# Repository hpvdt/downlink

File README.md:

# downlink
General data downlink system for our vehicles

## Known USB Issue

The STM32F103 series of microcontrollers needs an external 1.5&nbsp;kOhm pullup resistor to the 3.3&nbsp;V supply rail on the D+ line for proper used, as per table 3 in section 2.1 of [AN4879](https://www.st.com/resource/en/application_note/an4879-introduction-to-usb-hardware-and-pcb-guidelines-using-stm32-mcus-stmicroelectronics.pdf). 

This explains why previous boards failed to work with USB communications. The TITAN 2022 board managed to work because there was a 10&nbsp;kOhm resistor for this pullup, likely the minimum needed for this.

There is also no need for the 22&nbsp;Ohm resistors on the USB data lines.

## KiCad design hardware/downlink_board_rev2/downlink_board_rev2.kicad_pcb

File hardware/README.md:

# Hardware

These are the designs for the downlink board.

## USB Issues

After assembling V1.2 of the board, it was found trhat the USB functionality of the chip doesn't work. This issue seems to come from having the chip on the board, as flashing the code on STM32's on dev boards worked as intended. 

Further tests to try and isolate the root cause were inconclusive, installing a new chip didn't help; transplating a working chip from a dev board to this board failed, but worked when returned to its original dev board; running wires from a dev board to the 22 ohm resistors worked. So it seems to just affect chips that are mounted directly on the board.

So there is no known root cause, at least these boards can be used as RPi HATs until revised.

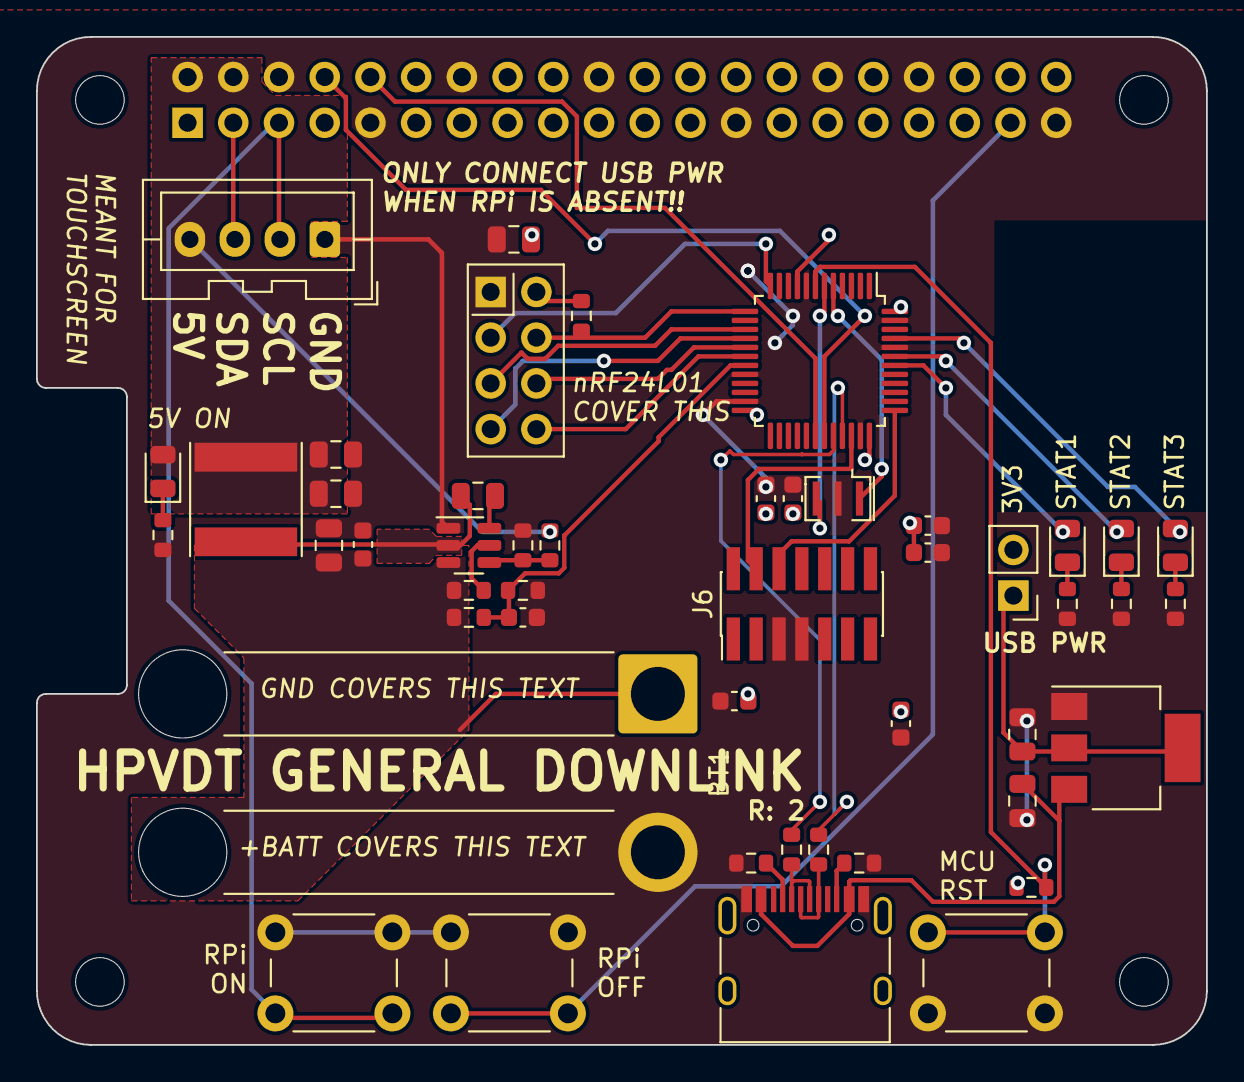
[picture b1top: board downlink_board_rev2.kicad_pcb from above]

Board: 2 copper layers, 65.0 x 56.0 mm, 53 parts (1 on the bottom side), 40 nets.

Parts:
BT1: Battery; SolderWire-2.5sqmm_1x02_P8.8mm_D2.4mm_OD4.4mm_Relief
C1, C2, C14: 10u; C_0805_2012Metric
C3, C8, C9, C10, C11, C13: 100n; C_0603_1608Metric
C4, C6, C7: 22u; C_0805_2012Metric
C5: 100n; C_0805_2012Metric
C12: 10n; C_0603_1608Metric
C15: 1u; C_0603_1608Metric
D1, D2, D3, D4: LED; LED_0805_2012Metric
J1: USB_C_Receptacle_USB2.0; USB_C_Receptacle_HRO_TYPE-C-31-M-12
J2: SCREEN; JST_XA_B04B-XASK-1_1x04_P2.50mm_Vertical
J3: GPIO; PinSocket_2x20_P2.54mm_Vertical
J6: Conn_ST_STDC14; PinHeader_2x07_P1.27mm_Vertical_SMD
JP1: USB_PWR; PinHeader_1x02_P2.54mm_Vertical
L1: 3u3; L_Taiyo-Yuden_NR-60xx
MH1, MH2, MH3, MH4: MountingHole_2.7mm_M2.5
R1, R2: 5.1k; R_0603_1608Metric
R3, R4: 22; R_0603_1608Metric
R5, R7, R13, R14, R16: 10k; R_0603_1608Metric
R6, R15: 54k9; R_0603_1608Metric
R8, R10, R11, R12: 330; R_0603_1608Metric
SW1: RPi_{ON}; SW_PUSH_6mm_H4.3mm
SW2: RPi_{OFF}; SW_PUSH_6mm_H4.3mm
SW3: MCU_{RST}; SW_PUSH_6mm_H4.3mm
U1: AZ1117-3.3; SOT-223-3_TabPin2
U2: TPS563208DDCR; TSOT-23-6
U3: STM32F103C8Tx; LQFP-48_7x7mm_P0.5mm
U4: nRF24L01; nRF24L01_Breakout
Y1: 8M; Resonator_SMD_Murata_CSTxExxV-3Pin_3.0x1.1mm

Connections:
+3.3V: C8.2, C9.2, C10.2, C11.2, C12.2, C14.2, C15.2, J3.1, J3.17, JP1.2 (B), R13.2, R14.2, U3.9 (VDDA), U3.24 (VDD), U3.36 (VDD), U3.48 (VDD), U4.2 (VCC)
+5V: C6.2, C7.2, D2.2 (A), J2.4, J3.2, J3.4, L1.2, R6.1
+BATT: BT1.1 (+), C1.2, C3.2, R5.1, R15.2, U2.3 (VIN)
/BATT_{DIV}: C13.2, R15.1, R16.2, U3.19 (PB1)
/D+: J1.A6 (D+), J1.B6 (D+), R4.1
/D-: J1.A7 (D-), J1.B7 (D-), R3.1
/FB: R6.2, R7.2, U2.4 (VFB)
/GPIO26: J3.37, SW2.2
/MISO: U3.16 (PA6), U4.7 (MISO)
/MOSI: U3.17 (PA7), U4.6 (MOSI)
/RF_{EN}: U3.12 (PA2), U4.3 (CE)
/RF_{INT}: U3.18 (PB0), U4.8 (IRQ)
/RF_{SEL}: R14.1, U3.13 (PA3), U4.4 (~CSN)
/RPi_{RX}: J3.10, U3.30 (PA9)
/RPi_{TX}: J3.8, U3.31 (PA10)
/RST_{MCU}: R13.1, SW3.2, U3.7 (NRST)
/SCK: U3.15 (PA5), U4.5 (SCK)
/SCL: J2.2, J3.5, SW1.2
/SDA: J2.3, J3.3
/SDWIO: J6.4 (JTMS/SWDIO), U3.34 (PA13)
/STATUS_{1}: D1.2 (A), U3.42 (PB6)
/STATUS_{2}: D3.2 (A), U3.43 (PB7)
/STATUS_{3}: D4.2 (A), U3.45 (PB8)
/SWCLK: J6.6 (JCLK/SWCLK), U3.37 (PA14)
/USB_D+: R4.2, U3.33 (PA12)
/USB_D-: R3.2, U3.32 (PA11)
GND: BT1.2 (-), C1.1, C2.1, C3.1, C4.1, C6.1, C7.1, C8.1, C9.1, C10.1, C11.1, C12.1, C13.1, C14.1, C15.1, J1.A1 (GND), J1.A12 (GND), J1.B1 (GND), J1.B12 (GND), J2.1, J3.6, J3.9, J3.14, J3.20, J3.25, J3.30, J3.34, J3.39, J6.5 (GND), J6.7 (GND), R1.2, R2.2, R7.1, R8.1, R10.1, R11.1, R12.1, R16.1, SW1.1, SW2.1, SW3.1, U1.1 (GND), U2.1 (GND), U3.8 (VSSA), U3.20 (PB2), U3.23 (VSS), U3.35 (VSS), U3.44 (BOOT0), U3.47 (VSS), U4.1 (GND), Y1.2
unnamed: D1.1 (K), R8.2
unnamed: D2.1 (K), R10.2
unnamed: D3.1 (K), R11.2
unnamed: D4.1 (K), R12.2
unnamed: J1.A5 (CC1), R1.1
unnamed: J1.B5 (CC2), R2.1
unnamed: C4.2, JP1.1 (A), U1.2 (VO)
unnamed: C2.2, J1.A4 (VBUS), J1.A9 (VBUS), J1.B4 (VBUS), J1.B9 (VBUS), U1.3 (VI)
unnamed: R5.2, U2.5 (EN)
unnamed: C5.2, L1.1, U2.2 (SW)
unnamed: C5.1, U2.6 (VBST)
unnamed: U3.5 (PD0), Y1.1
unnamed: U3.6 (PD1), Y1.3

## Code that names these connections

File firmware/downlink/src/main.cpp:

#include <Arduino.h>

#ifdef STM32
HardwareSerial RPi(PA10, PA9);
#define Serial RPi
#endif

const int ledPins[] = {PB6, PB7, PB8};

void setup() {
  for (int i = 0; i < 3; i++) pinMode(ledPins[i], OUTPUT);
  Serial.begin(115200);
  for (int i = 0; i < 3; i++) digitalWrite(ledPins[i], HIGH);
}

void loop() {
  for (int i = 0; i < 3; i++) digitalWrite(ledPins[i], HIGH);
  delay(1000);
  for (int i = 0; i < 3; i++) digitalWrite(ledPins[i], LOW);
  delay(1000);
  Serial.println(millis());
}

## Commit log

2023-11-30 Completed initial schematic
2023-11-30 Added PWM message for LEDs
2023-12-05 Revised input caps for vreg
2023-12-05 Completed Rev 1.0 layout
2023-12-05 Layout Rev 1.1
    Added a keepout area under where the antenna header will go to ensure that if it scratches the board no shorts will occur.
2023-12-06 Layout V1.2, no more USB overhang
2023-12-06 Changed folder organization
2023-12-19 BOM adjustments
2023-12-19 Added for hardware files
2024-01-18 Upload of baseline firmware
2024-01-21 Recording USB issues
2024-01-22 Updated schematic with warning
2024-01-22 Basic serial code tests
2024-06-14 Initial commit of rev2 downlink
2024-07-06 Updated to Rev 2
2024-07-06 Updated the debugger header connections
    Added TX RX connection with the header
    Deleted BOOT1
2024-07-08 Finished rerouting everything
    rerouted everything, resolved the hardware conflict between the header and the NRF module.
2024-07-09 Update on reroutes
    Updated the routing such that the routes doesn't go to the edge of the board just in case.
2024-07-16 Updated PCB & slight rerouting
    Updated PCB to match schematic headers; moved microcontroller closer to USB port
2024-07-16 Moved caps closer to microcontroller
    Moved the four 100nF capacitors closer to the microcontroller (had previously mistakenly moved them farther away)
2024-07-16 Minor relocation of 10n, 1u caps
2026-04-22 Document known USB issue for STM32F103
    Added information about USB issues related to STM32F103 microcontrollers.
